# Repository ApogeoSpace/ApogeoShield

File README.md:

# ApogeoShield

This repository hosts design files for an Arduino shield featuring a HopeRF RFM98 module, optimized for communication at 169 MHz. 
The project is developed by Apogeo Space Srl and allows users to connect and communicate via LoRa with the Apogeo Space IoT network with their own hardware.

## Building your shield

Feel free to utilize the provided files to construct your shields, ensuring compliance with the terms of our [license](LICENSE.md).

Please note that the project is built using KiCad 6, and while compatibility has been tested with later versions, successful importation to other CAD software is not guaranteed.

### BOM

While we do not provide specific sources for all the components needed; however, you can find the actual [BOM](bom.csv) and refer to it when sourcing components.

You can also open an issue or contact us directly for more information if you find it difficult to find certain components.

## What can I do with it?

Once you have built a shield, you can mount it on an Arduino Uno and use our [ApogeoNode](https://github.com/ApogeoSpace/ApogeoNode) library to connect to the Apogeo Space IoT network!

For further information or inquiries, please contact us.

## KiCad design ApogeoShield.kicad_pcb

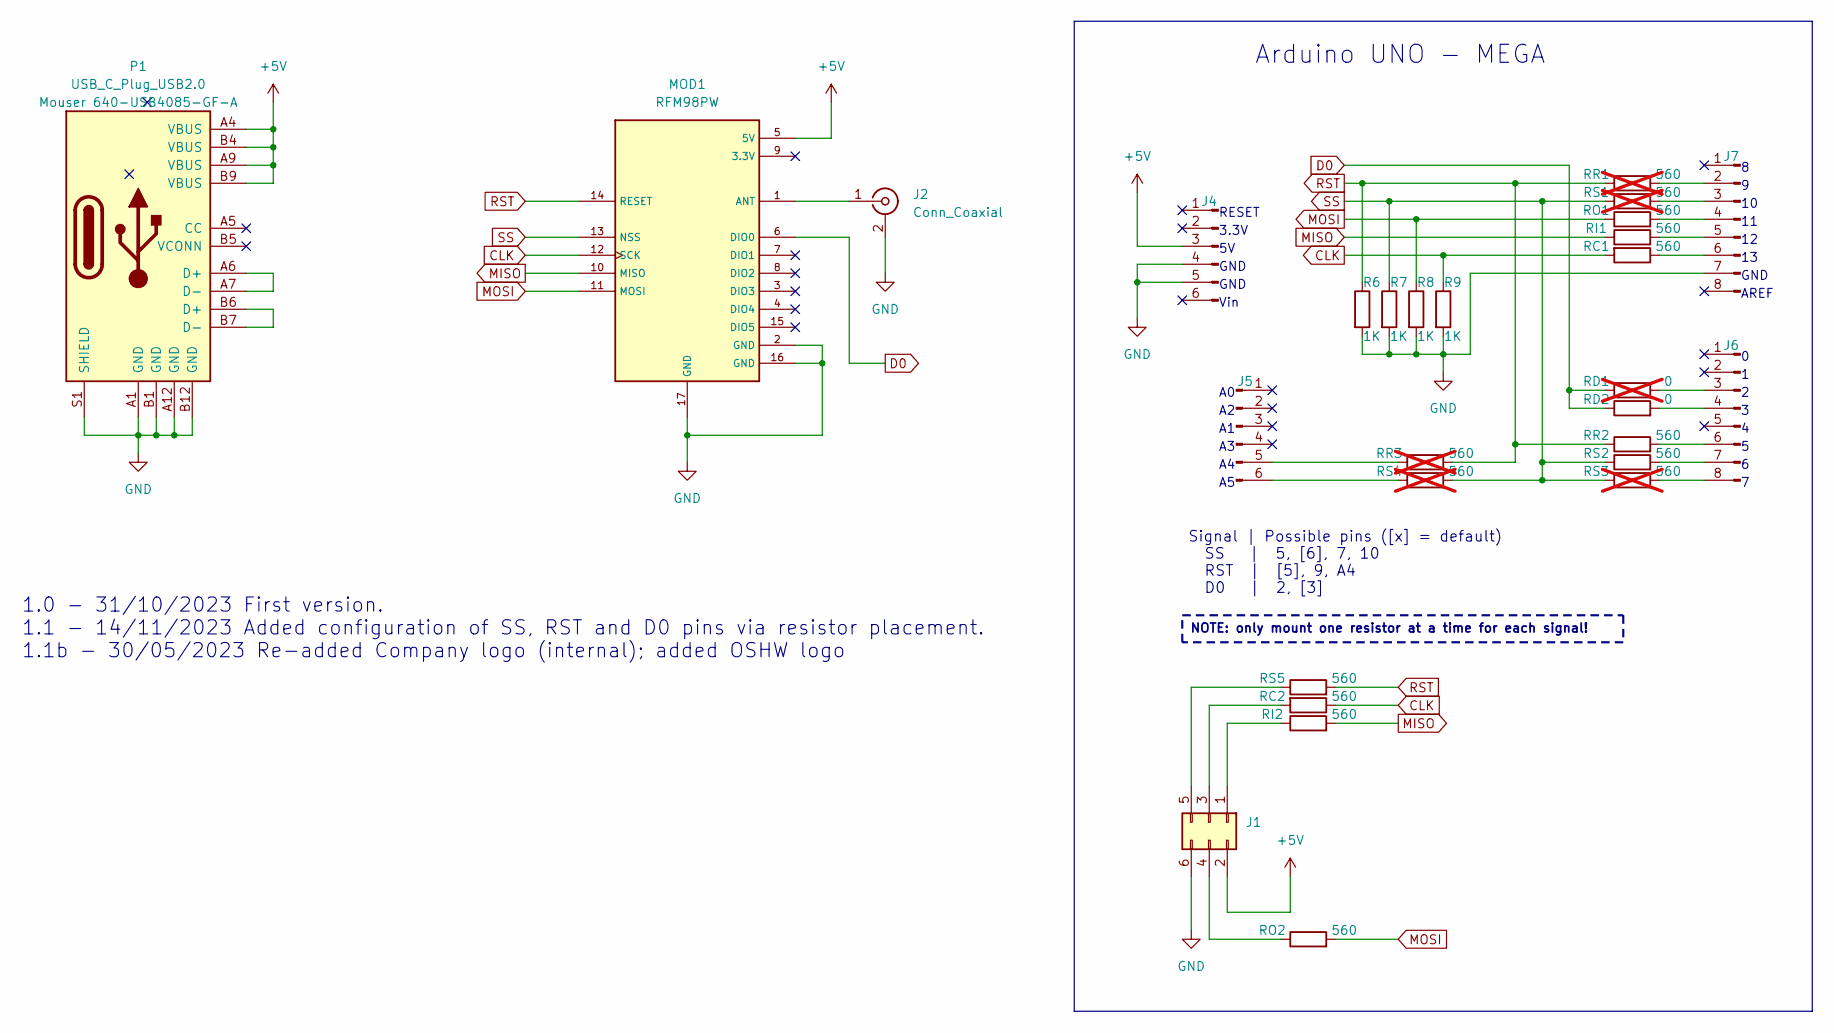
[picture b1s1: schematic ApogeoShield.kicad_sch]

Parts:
J1: Conn_02x03_Odd_Even; PinHeader_2x03_P2.54mm_Vertical
J2: Conn_Coaxial; SMA_Amphenol_901-143_Horizontal
J4, J5: Conn_01x06_Pin; PinHeader_1x06_P2.54mm_Vertical
J6, J7: Conn_01x08_Pin; PinHeader_1x08_P2.54mm_Vertical
MOD1: RFM98PW; XCVR_RFM98PW
P1: USB_C_Plug_USB2.0; USB_C_Receptacle_GCT_USB4085
R6, R7, R8, R9: 1K; R_1206_3216Metric_Pad1.30x1.75mm_HandSolder
RC1, RC2: 560; R_1206_3216Metric_Pad1.30x1.75mm_HandSolder
RD1: 0; R_1206_3216Metric_Pad1.30x1.75mm_HandSolder; not fitted
RD2: 0; R_1206_3216Metric_Pad1.30x1.75mm_HandSolder
RI1, RI2: 560; R_1206_3216Metric_Pad1.30x1.75mm_HandSolder
RO1, RO2: 560; R_1206_3216Metric_Pad1.30x1.75mm_HandSolder
RR1, RR3: 560; R_1206_3216Metric_Pad1.30x1.75mm_HandSolder; not fitted
RR2: 560; R_1206_3216Metric_Pad1.30x1.75mm_HandSolder
RS1, RS3, RS4: 560; R_1206_3216Metric_Pad1.30x1.75mm_HandSolder; not fitted
RS2, RS5: 560; R_1206_3216Metric_Pad1.30x1.75mm_HandSolder

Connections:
+5V: J1.2, J4.3, MOD1.5 (5V), P1.A4 (VBUS), P1.A9 (VBUS), P1.B4 (VBUS), P1.B9 (VBUS)
CLK: MOD1.12 (SCK), R9.1, RC1.2, RC2.1
D0: MOD1.6 (DIO0), RD1.1, RD2.1
GND: J1.6, J2.2 (Ext), J4.4, J4.5, J7.7, MOD1.2 (GND), MOD1.16 (GND), MOD1.17 (GND), P1.A1 (GND), P1.A12 (GND), P1.B1 (GND), P1.B12 (GND), P1.S1 (SHIELD), R6.2, R7.2, R8.2, R9.2
MISO: MOD1.10 (MISO), RI1.1, RI2.2
MOSI: MOD1.11 (MOSI), R8.1, RO1.1, RO2.2
unnamed: J1.1, RI2.1
unnamed: J1.3, RC2.2
unnamed: J1.4, RO2.1
unnamed: J1.5, RS5.1
unnamed: J2.1 (In), MOD1.1 (ANT)
unnamed: J5.5, RR3.1
unnamed: J5.6, RS4.1
unnamed: J6.3, RD1.2
unnamed: J6.4, RD2.2
unnamed: J6.6, RR2.2
unnamed: J6.7, RS2.2
unnamed: J6.8, RS3.2
unnamed: J7.2, RR1.2
unnamed: J7.3, RS1.2
unnamed: J7.4, RO1.2
unnamed: J7.5, RI1.2
unnamed: J7.6, RC1.1
unnamed: P1.A6 (D+), P1.A7 (D-)
unnamed: P1.B6 (D+), P1.B7 (D-)
RST: MOD1.14 (RESET), R6.1, RR1.1, RR2.1, RR3.2, RS5.2
SS: MOD1.13 (NSS), R7.1, RS1.1, RS2.1, RS3.1, RS4.2

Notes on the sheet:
NOTE: only mount one resistor at a time for each signal!
Vin
3.3V
Arduino UNO - MEGA
GND
Signal | Possible pins ([x] = default) SS | 5, [6], 7, 10 RST | [5], 9, A4 D0 | 2, [3]
RESET
AREF
1.0 - 31/10/2023 First version. 1.1 - 14/11/2023 Added configuration of SS, RST and D0 pins via resistor placement. 1.1b - 30/05/2023 Re-added Company logo (internal); added OSHW logo

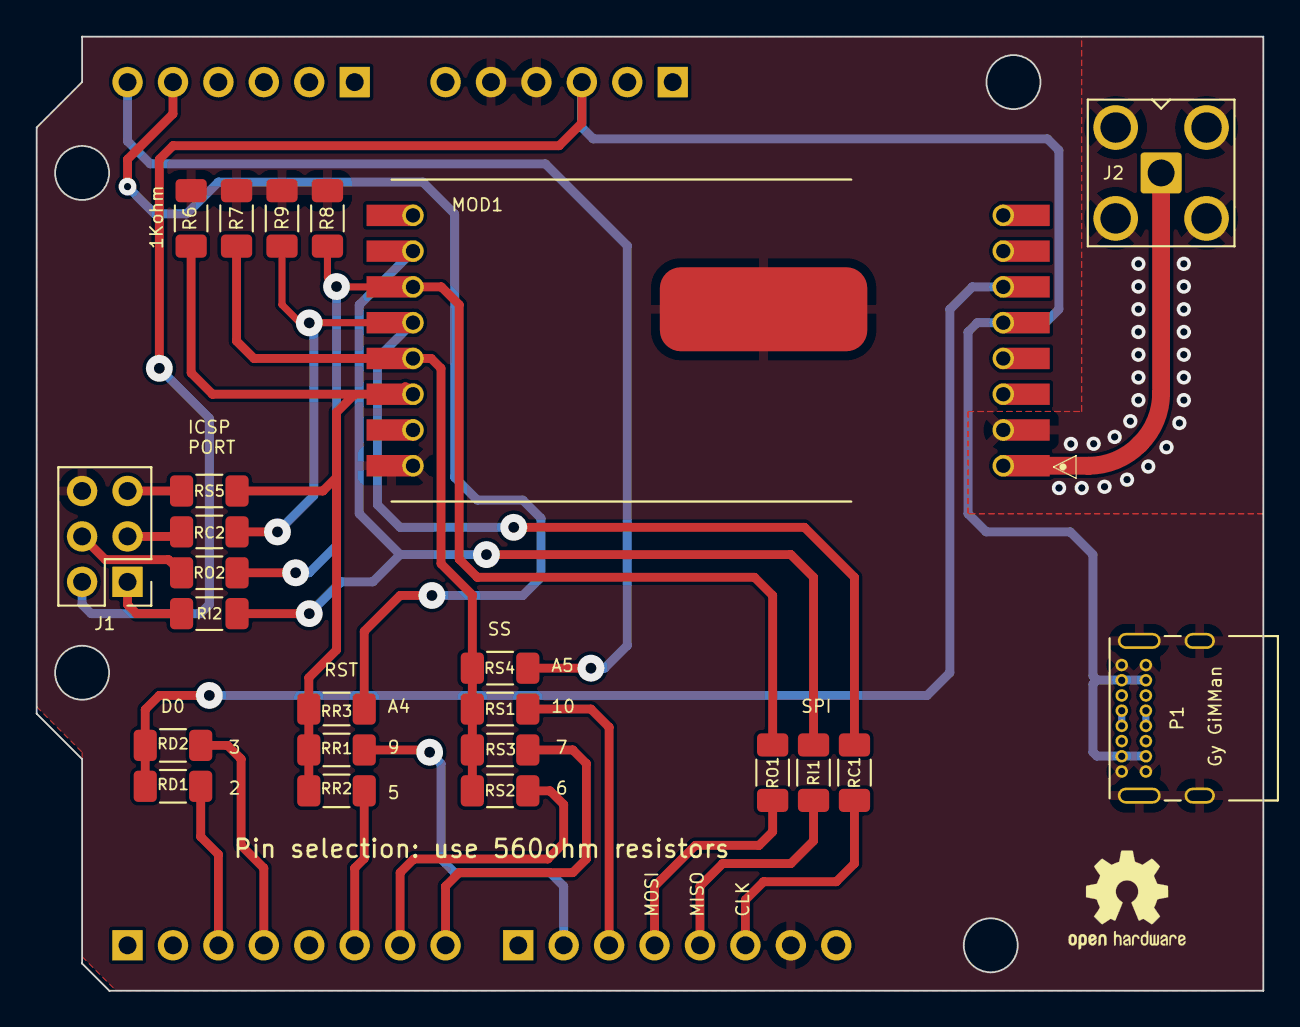
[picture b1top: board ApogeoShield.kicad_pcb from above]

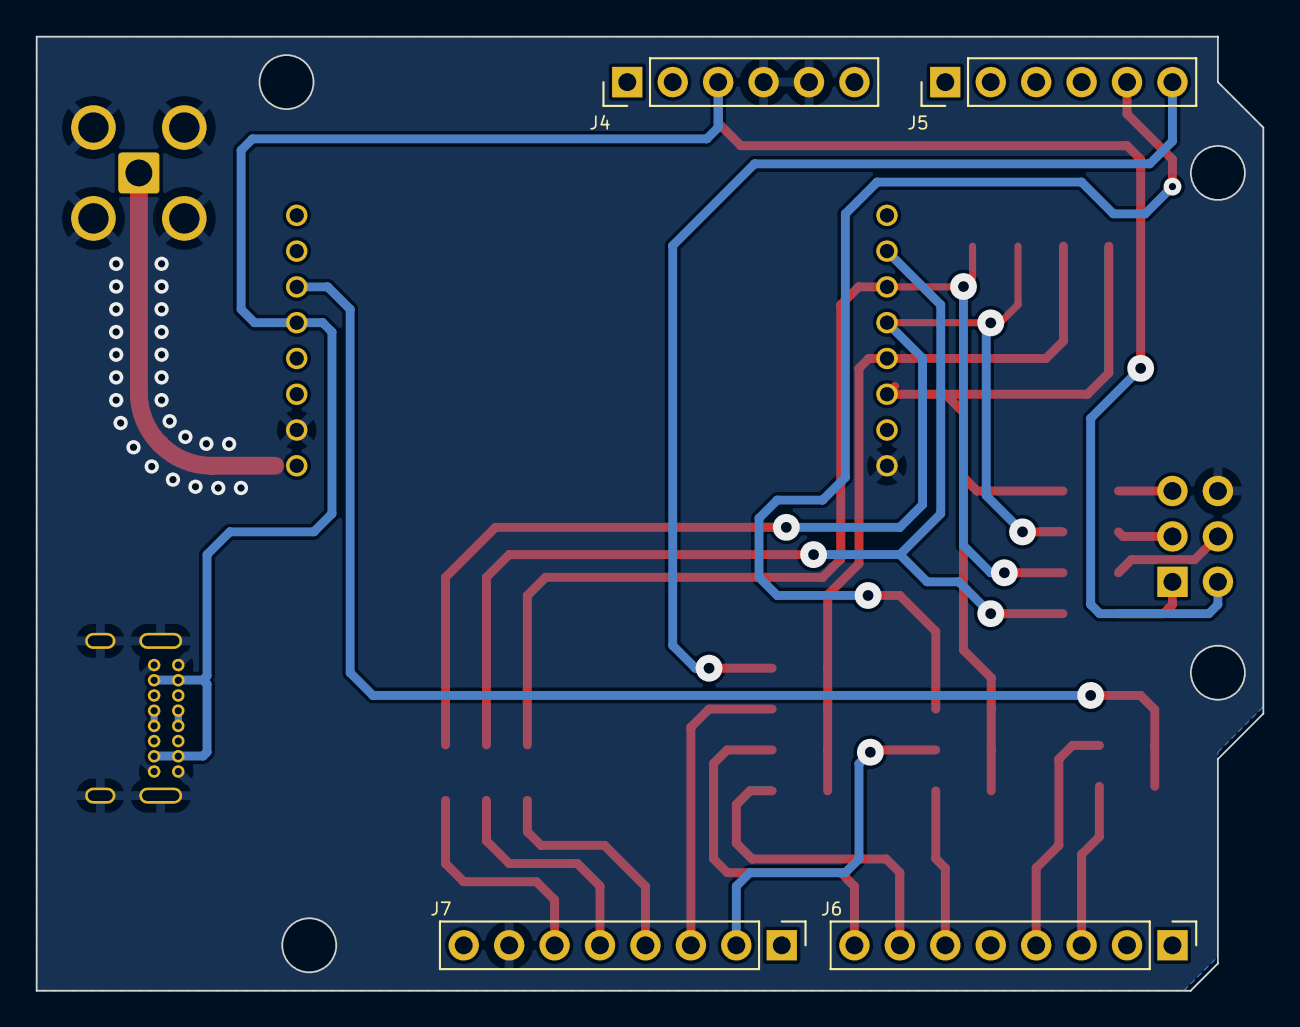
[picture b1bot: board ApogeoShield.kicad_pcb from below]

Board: 2 copper layers, 68.6 x 53.3 mm, 28 parts (4 on the bottom side), 27 nets.

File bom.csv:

"Reference","Value","Datasheet","Footprint","Qty","DNP"
"J1","Conn_02x03_Odd_Even","~","Connector_PinHeader_2.54mm:PinHeader_2x03_P2.54mm_Vertical","1",""
"J2","Conn_Coaxial"," ~","Amphenol:SMA_Amphenol_901-143_Horizontal","1",""
"J4,J5","Conn_01x06_Pin","~","Connector_PinHeader_2.54mm:PinHeader_1x06_P2.54mm_Vertical","2",""
"J6,J7","Conn_01x08_Pin","~","Connector_PinHeader_2.54mm:PinHeader_1x08_P2.54mm_Vertical","2",""
"MOD1","RFM98PW","","Acies:XCVR_RFM98PW","1",""
"P1","USB_C_Plug_USB2.0","https://www.usb.org/sites/default/files/documents/usb_type-c.zip","Connettori_P:USB_C_Receptacle_GCT_USB4085","1",""
"R6,R7,R8,R9","1K","~","Resistor_SMD:R_1206_3216Metric_Pad1.30x1.75mm_HandSolder","4",""
"RC1,RC2,RI1,RI2,RO1,RO2,RR2,RS2,RS5","560","~","Resistor_SMD:R_1206_3216Metric_Pad1.30x1.75mm_HandSolder","9",""
"RD2","0","~","Resistor_SMD:R_1206_3216Metric_Pad1.30x1.75mm_HandSolder","1",""

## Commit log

2024-03-15 Initial commit on releases branch
2024-03-15 Release 0.1
2024-05-30 Release 1.1b
